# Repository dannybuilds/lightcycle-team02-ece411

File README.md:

# lightcycle-team02-ece411
A repository that'll host the documentation, support info, and source files for Team 02's practicum project.

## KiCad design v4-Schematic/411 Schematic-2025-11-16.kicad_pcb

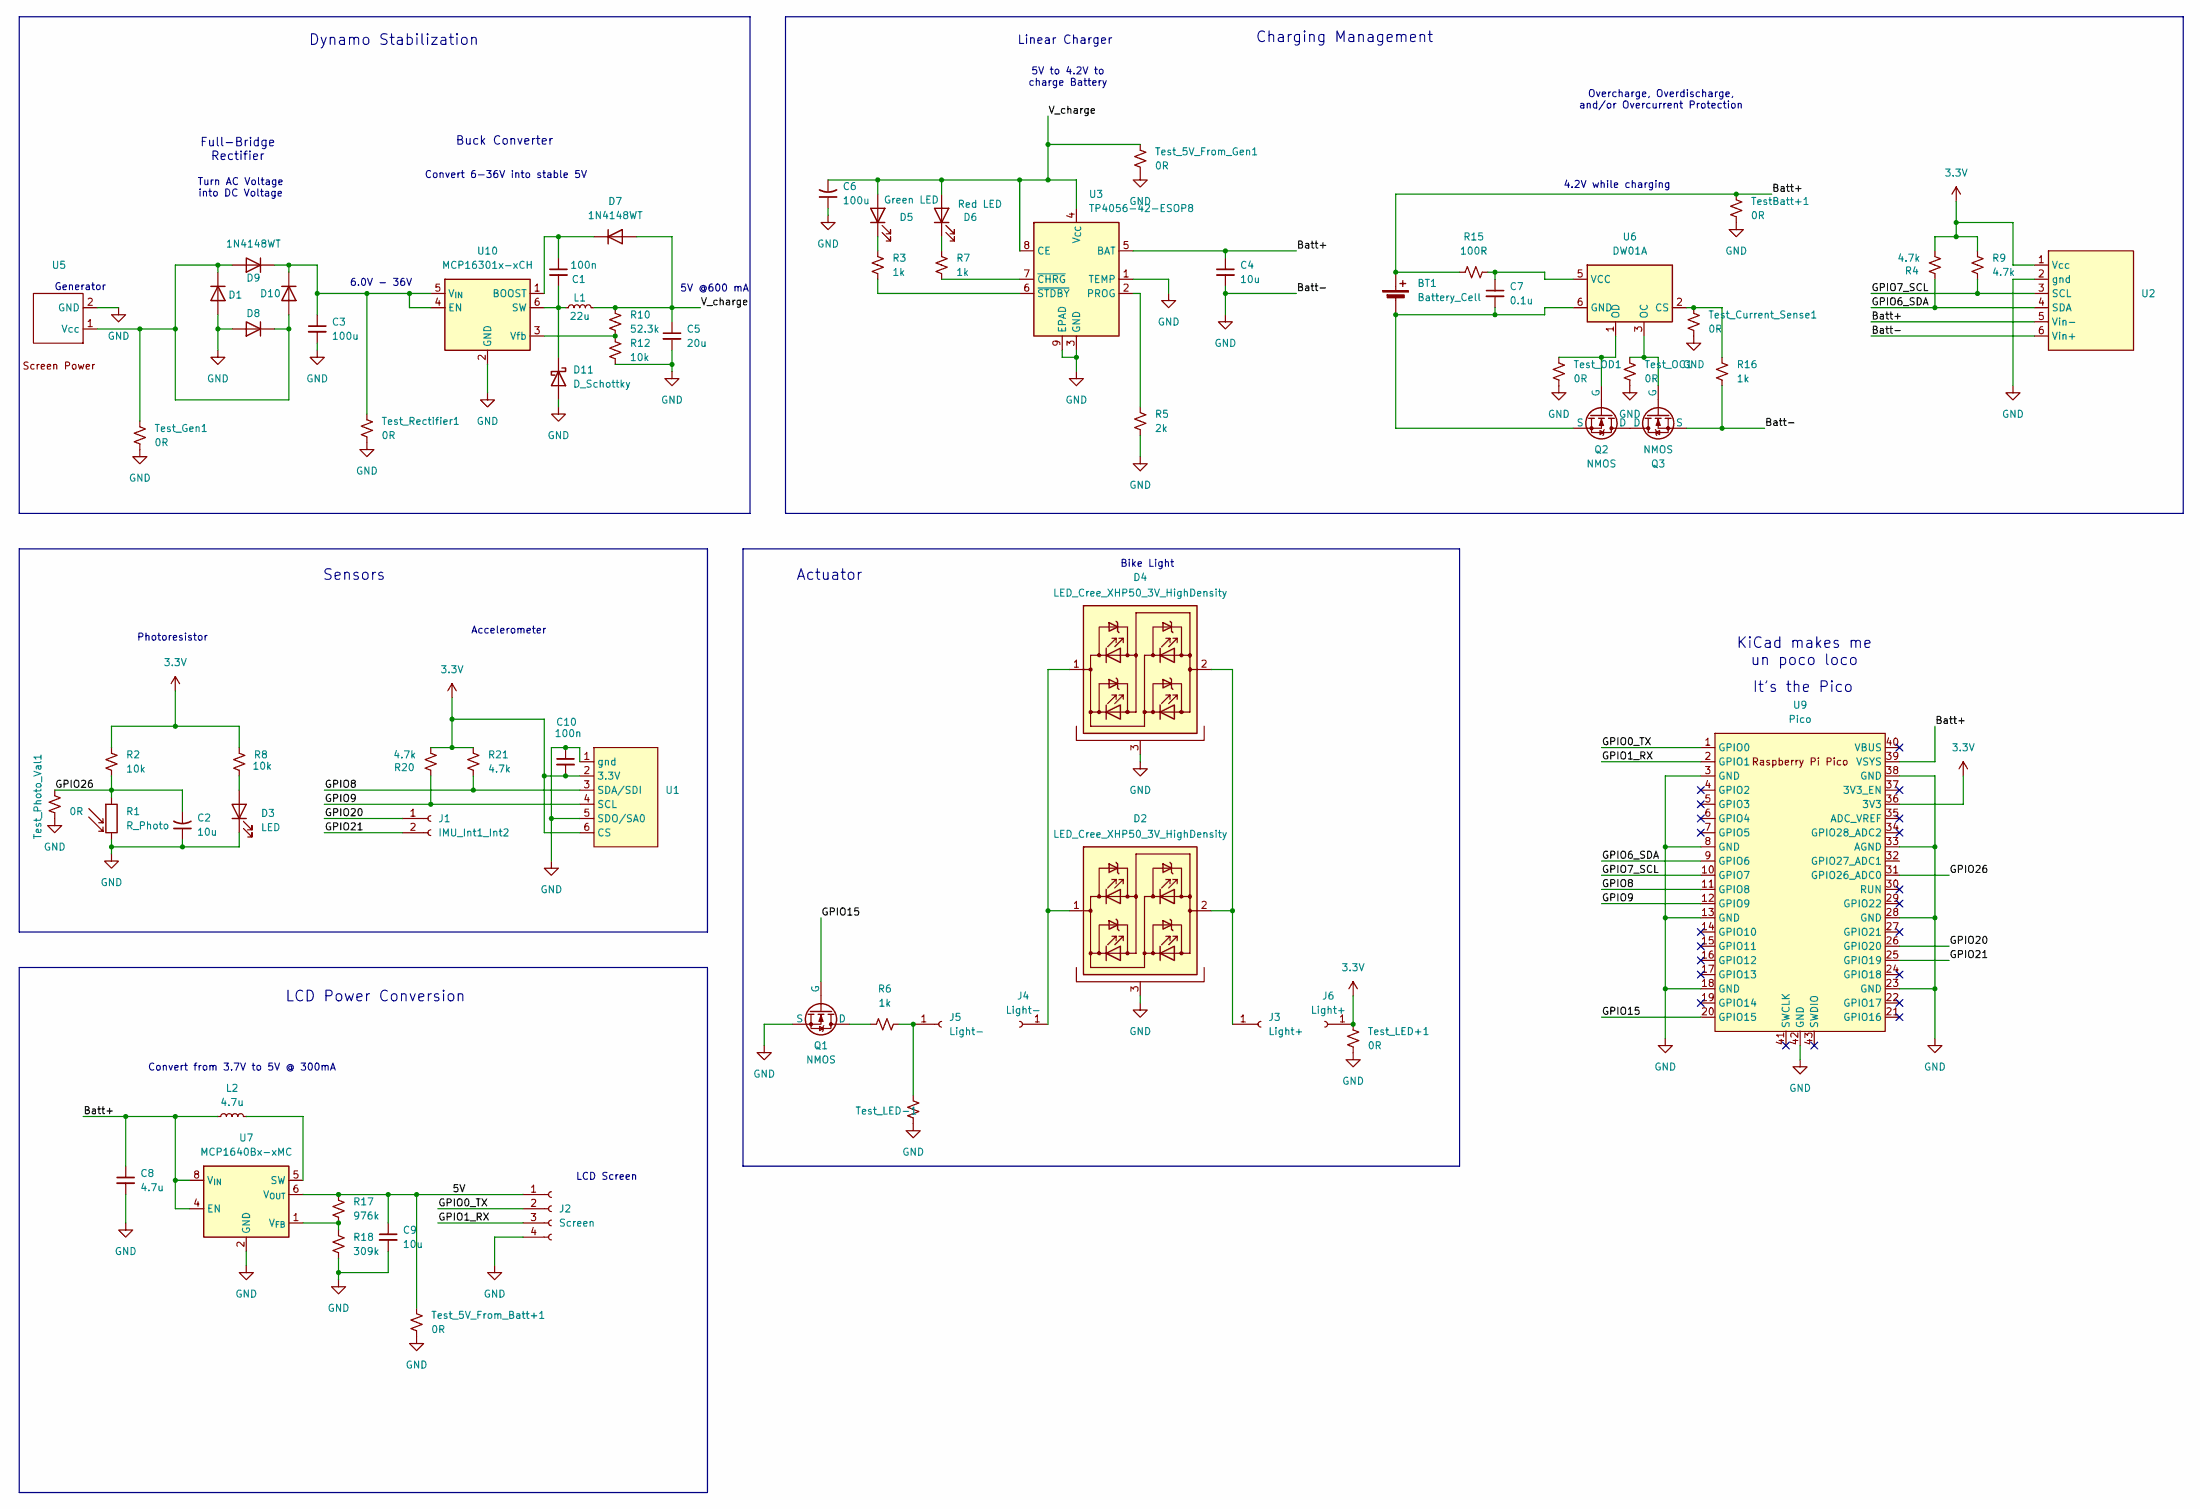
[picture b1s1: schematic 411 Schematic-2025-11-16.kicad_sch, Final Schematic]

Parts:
BT1: Battery_Cell; LED_D3.0mm_Clear
C1, C10: 100n; CP_Radial_D4.0mm_P2.00mm
C2, C4, C9: 10u; CP_Radial_D4.0mm_P2.00mm
C3, C6: 100u; CP_Radial_D4.0mm_P2.00mm
C5: 20u; CP_Radial_D4.0mm_P2.00mm
C7: 0.1u; CP_Radial_D4.0mm_P2.00mm
C8: 4.7u; CP_Radial_D4.0mm_P2.00mm
D1, D7, D8, D9, D10: 1N4148WT; LED_D3.0mm_Clear
D2, D4: LED_Cree_XHP50_3V_HighDensity; LED_Cree-XHP50_3V_HighDensity
D3: LED; LED_D3.0mm_Clear
D5: Green LED; LED_D3.0mm_Clear
D6: Red LED; LED_D3.0mm_Clear
D11: D_Schottky; D_A-405_P7.62mm_Horizontal
J1: IMU_Int1_Int2; PinHeader_2x01_P2.00mm_Vertical
J2: Screen; JST_EH_B6B-EH-A_1x06_P2.50mm_Vertical
J3, J6: Light+; Pin_D0.7mm_L6.5mm_W1.8mm_FlatFork
J4, J5: Light-; Pin_D0.7mm_L6.5mm_W1.8mm_FlatFork
L1: 22u; L_Wuerth_WE-PD-Typ-7345
L2: 4.7u; L_Wuerth_WE-PD-Typ-7345
Q1, Q2, Q3: NMOS; TO-92L_Inline_Wide
R1: R_Photo; R_LDR_4.9x4.2mm_P2.54mm_Vertical
R2, R8, R12: 10k; R_Axial_DIN0207_L6.3mm_D2.5mm_P10.16mm_Horizontal
R3, R6, R7, R16: 1k; R_Axial_DIN0207_L6.3mm_D2.5mm_P10.16mm_Horizontal
R4, R9, R20, R21: 4.7k; R_Axial_DIN0207_L6.3mm_D2.5mm_P10.16mm_Horizontal
R5: 2k; R_Axial_DIN0207_L6.3mm_D2.5mm_P10.16mm_Horizontal
R10: 52.3k; R_Axial_DIN0207_L6.3mm_D2.5mm_P10.16mm_Horizontal
R15: 100R; R_Axial_DIN0207_L6.3mm_D2.5mm_P10.16mm_Horizontal
R17: 976k; R_Axial_DIN0207_L6.3mm_D2.5mm_P10.16mm_Horizontal
R18: 309k; R_Axial_DIN0207_L6.3mm_D2.5mm_P10.16mm_Horizontal
TestBatt+1: 0R; R_0603_1608Metric_Pad0.98x0.95mm_HandSolder
Test_5V_From_Batt+1, Test_5V_From_Gen1: 0R; R_0603_1608Metric_Pad0.98x0.95mm_HandSolder
Test_Current_Sense1: 0R; R_0603_1608Metric_Pad0.98x0.95mm_HandSolder
Test_Gen1: 0R; R_0603_1608Metric_Pad0.98x0.95mm_HandSolder
Test_LED+1: 0R; R_0603_1608Metric_Pad0.98x0.95mm_HandSolder
Test_LED-1: 0R; R_0603_1608Metric_Pad0.98x0.95mm_HandSolder
Test_OC1: 0R; R_0603_1608Metric_Pad0.98x0.95mm_HandSolder
Test_OD1: 0R; R_0603_1608Metric_Pad0.98x0.95mm_HandSolder
Test_Photo_Val1: 0R; R_0603_1608Metric_Pad0.98x0.95mm_HandSolder
Test_Rectifier1: 0R; R_0603_1608Metric_Pad0.98x0.95mm_HandSolder
U1, U2, U5: JST_EH_B6B-EH-A_1x06_P2.50mm_Vertical
U3: TP4056-42-ESOP8; SOIC-8-1EP_3.9x4.9mm_P1.27mm_EP2.41x3.3mm_ThermalVias
U6: DW01A; SOT-23-6
U7: MCP1640Bx-xMC; DFN-8-1EP_3x2mm_P0.5mm_EP1.75x1.45mm
U9: Pico; RPi_Pico_SMD_TH
U10: MCP16301x-xCH; SOT-23-6

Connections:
3.3V: C10.2, J6.1, R2.1, R4.1, R8.1, R9.2, R20.1, R21.2, Test_LED+1.2, U1.2 (3.3V), U1.6 (CS), U2.1 (Vcc), U9.36 (3V3)
/5V: C9.1, J2.1, R17.1, Test_5V_From_Batt+1.2, U7.6 (V_{OUT}), U7.7 (V_{OUT})
/Batt+: BT1.1 (+), C4.1, C8.1, L2.1, R15.1, TestBatt+1.2, U2.5 (Vin-), U3.5 (BAT), U7.4 (EN), U7.8 (V_{IN}), U9.39 (VSYS)
/GPIO0_TX: J2.2, U9.1 (GPIO0)
/GPIO1_RX: J2.3, U9.2 (GPIO1)
/GPIO6_SDA: R4.2, U2.4 (SDA), U9.9 (GPIO6)
/GPIO7_SCL: R9.1, U2.3 (SCL), U9.10 (GPIO7)
/GPIO8: R21.1, U1.3 (SDA/SDI), U9.11 (GPIO8)
/GPIO9: R20.2, U1.4 (SCL), U9.12 (GPIO9)
/GPIO15: Q1.2 (G), U9.20 (GPIO15)
/GPIO20: J1.1, U9.26 (GPIO20)
/GPIO21: J1.2, U9.25 (GPIO19)
/GPIO26: C2.2, R1.1, R2.2, Test_Photo_Val1.2, U9.31 (GPIO26_ADC0)
/GPIO27: U9.32 (GPIO27_ADC1)
/V_charge: C5.1, C6.2, D5.2 (A), D6.2 (A), D7.2 (A), L1.2, R10.1, Test_5V_From_Gen1.2, U3.4 (V_{CC}), U3.8 (CE)
GND: C2.1, C3.2, C4.2, C5.2, C6.1, C8.2, C9.2, C10.1, D1.2 (A), D2.3 (PAD), D3.1 (K), D4.3 (PAD), D8.2 (A), D11.2 (A), J2.4, Q1.3 (S), Q3.3 (S), R1.2, R5.2, R12.2, R16.1, R18.2, TestBatt+1.1, Test_5V_From_Batt+1.1, Test_5V_From_Gen1.1, Test_Current_Sense1.1, Test_Gen1.1, Test_LED+1.1, Test_LED-1.1, Test_OC1.1, Test_OD1.1, Test_Photo_Val1.1, Test_Rectifier1.1, U1.1 (gnd), U1.5 (SDO/SA0), U2.2 (gnd), U2.6 (Vin+), U3.1 (TEMP), U3.3 (GND), U3.9 (EPAD), U5.2 (GND), U7.2 (GND), U7.3 (GND), U7.9 (GND), U9.3 (GND), U9.8 (GND), U9.13 (GND), U9.18 (GND), U9.23 (GND), U9.28 (GND), U9.33 (AGND), U9.38 (GND), U9.42 (GND), U10.2 (GND)
unnamed: BT1.2 (-), C7.2, Q2.3 (S), U6.6 (GND)
unnamed: D1.1 (K), D8.1 (K), D9.2 (A), D10.2 (A), Test_Gen1.2, U5.1 (Vcc)
unnamed: D2.2 (A), D4.2 (A), J3.1
unnamed: D2.1 (K), D4.1 (K), J4.1
unnamed: D3.2 (A), R8.2
unnamed: D5.1 (K), R3.1
unnamed: D6.1 (K), R7.1
unnamed: C1.1, D7.1 (K), U10.1 (BOOST)
unnamed: C3.1, D9.1 (K), D10.1 (K), Test_Rectifier1.2, U10.4 (EN), U10.5 (V_{IN})
unnamed: C1.2, D11.1 (K), L1.1, U10.6 (SW)
unnamed: J5.1, R6.2, Test_LED-1.2
unnamed: Q1.1 (D), R6.1
unnamed: Q2.1 (D), Q3.1 (D)
unnamed: Q2.2 (G), Test_OD1.2, U6.1 (OD)
unnamed: Q3.2 (G), Test_OC1.2, U6.3 (OC)
unnamed: R5.1, U3.2 (PROG)
unnamed: R7.2, U3.7 (~CHRG)
unnamed: R3.2, U3.6 (~STDBY)
unnamed: R16.2, Test_Current_Sense1.2, U6.2 (CS)
unnamed: C7.1, R15.2, U6.5 (VCC)
unnamed: L2.2, U7.5 (SW)
unnamed: R17.2, R18.1, U7.1 (V_{FB})
unnamed: R10.2, R12.1, U10.3 (Vfb)

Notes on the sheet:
Dynamo Stabilization
Buck Converter
Convert from 3.7V to 5V @ 300mA
Overcharge, Overdischarge, and/or Overcurrent Protection
Actuator
KiCad makes me un poco loco
Full-Bridge Rectifier
It's the Pico
6.0V - 36V
Accelerometer
LCD Power Conversion
Convert 6-36V into stable 5V
Linear Charger
LCD Screen
Sensors
5V @600 mA
Turn AC Voltage into DC Voltage
Photoresistor
Generator
5V to 4.2V to charge Battery
Charging Management
Bike Light
4.2V while charging

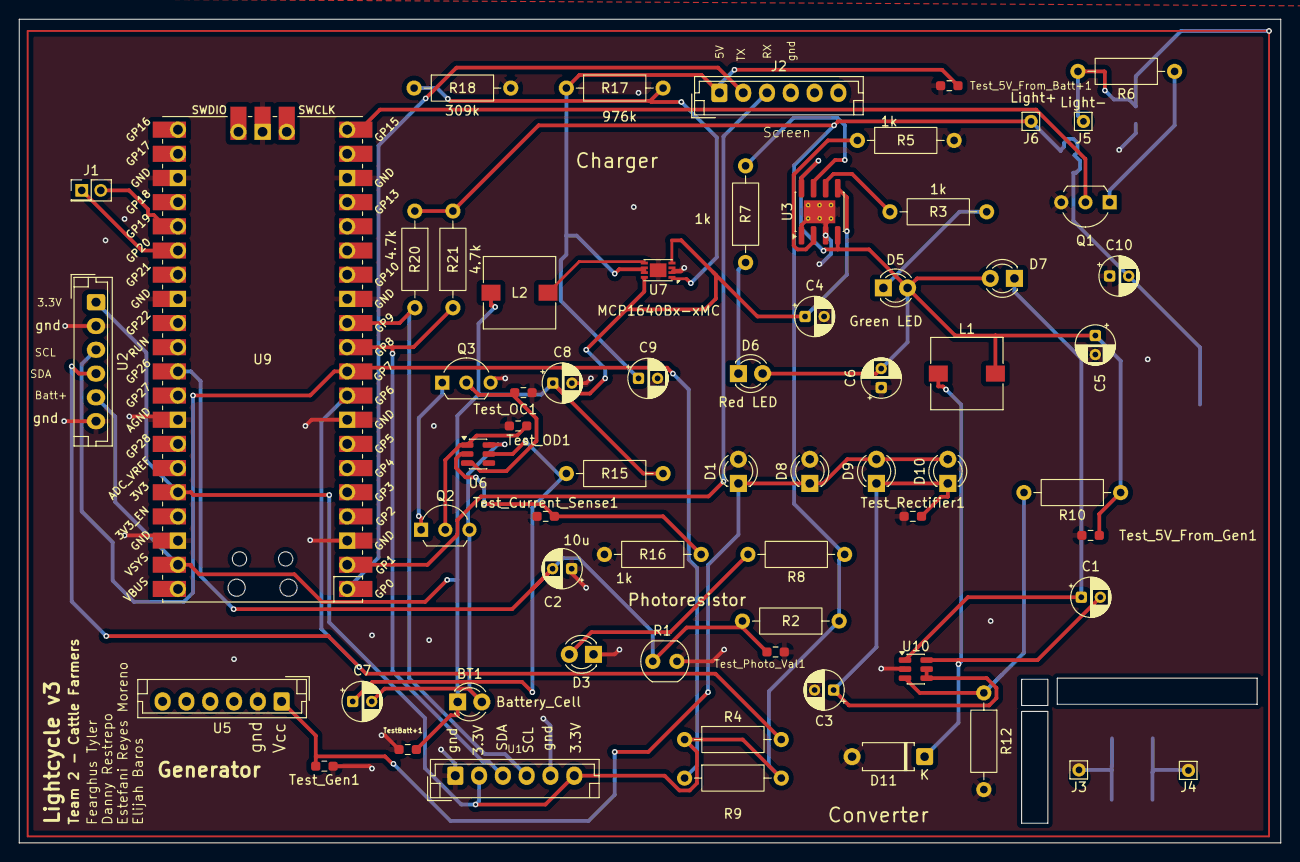
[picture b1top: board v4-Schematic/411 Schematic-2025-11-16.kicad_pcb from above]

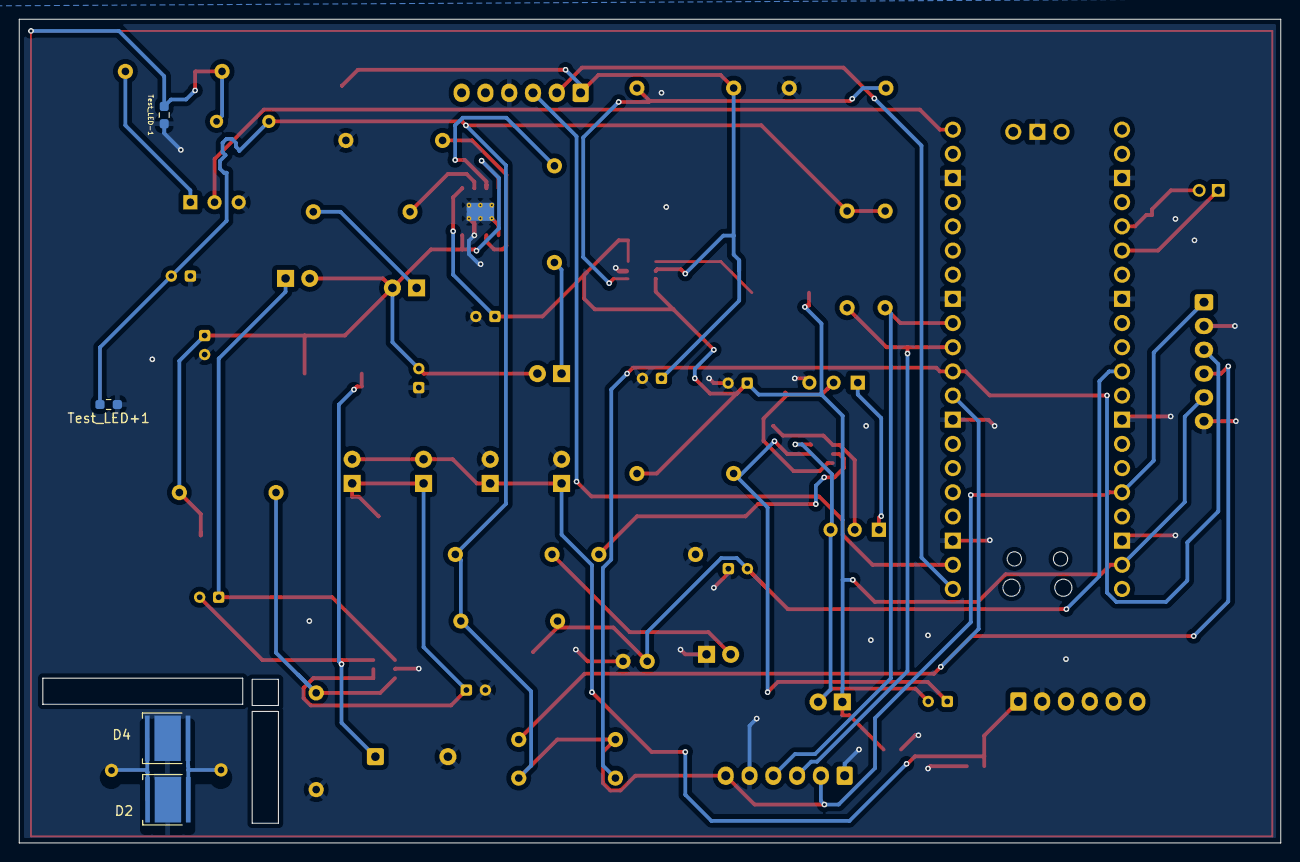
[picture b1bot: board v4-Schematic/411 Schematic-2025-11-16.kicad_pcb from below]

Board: 2 copper layers, 132.5 x 86.5 mm, 69 parts (4 on the bottom side), 38 nets.

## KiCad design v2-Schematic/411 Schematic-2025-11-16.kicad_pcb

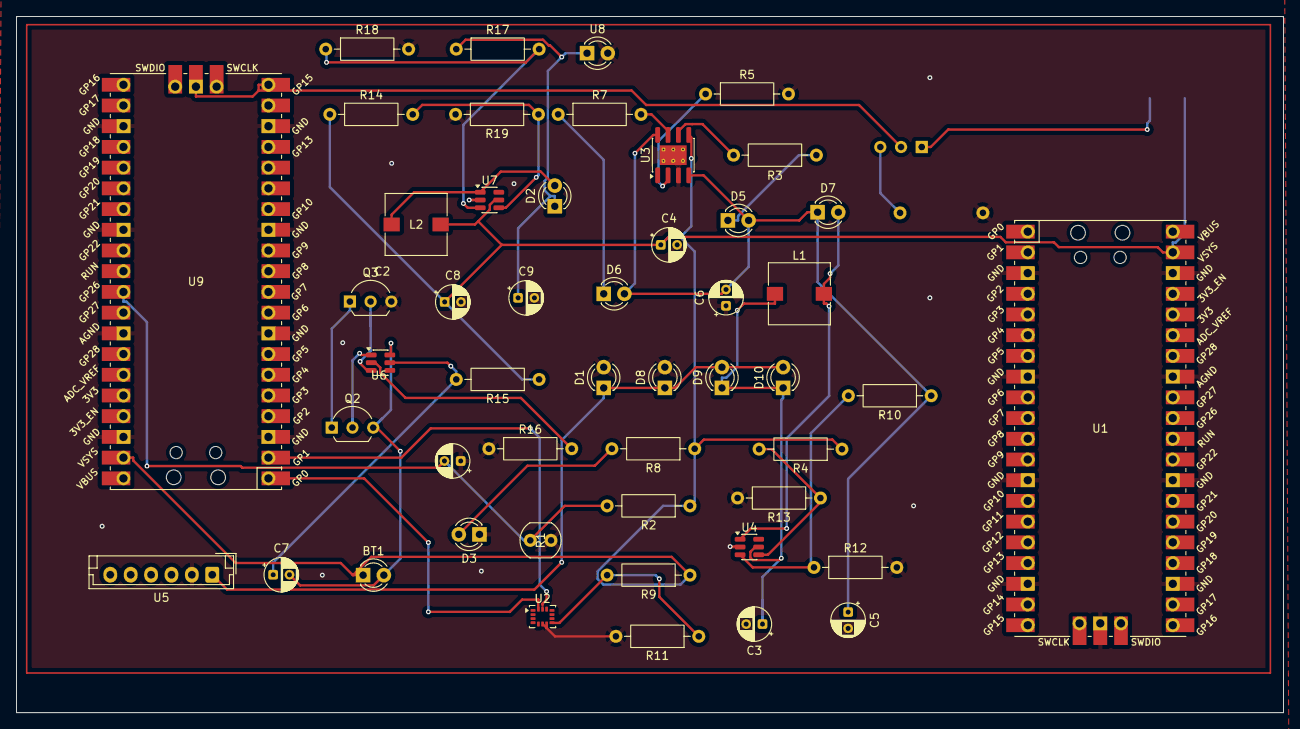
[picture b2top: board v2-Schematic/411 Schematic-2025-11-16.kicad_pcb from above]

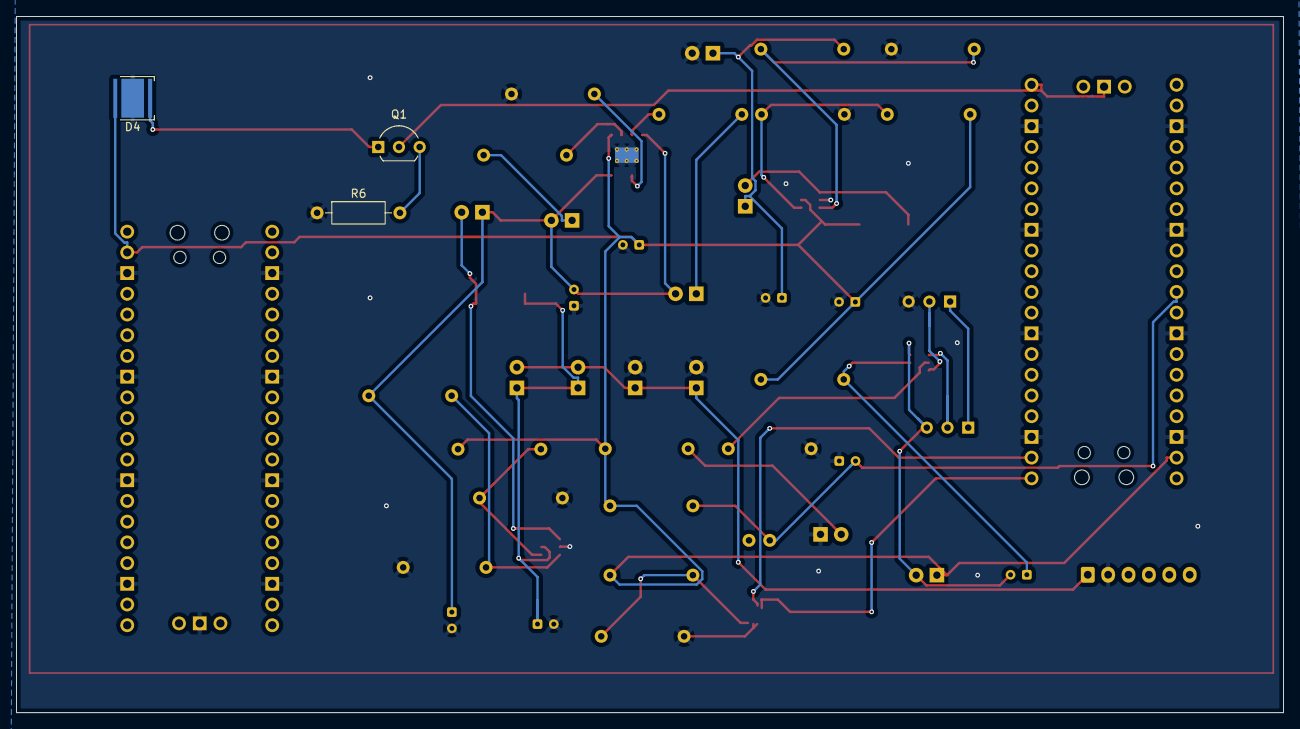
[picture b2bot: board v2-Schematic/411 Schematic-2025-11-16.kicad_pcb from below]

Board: 2 copper layers, 155.4 x 85.4 mm, 52 parts (3 on the bottom side), 31 nets.

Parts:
BT1: Battery_Cell; LED_D3.0mm_Clear
C2, C4: 10u; CP_Radial_D4.0mm_P2.00mm
C3, C5, C6, C8, C9: 100u; CP_Radial_D4.0mm_P2.00mm
C7: 0.1u; CP_Radial_D4.0mm_P2.00mm
D1, D2, D7, D8, D9, D10: 1N4148WT; LED_D3.0mm_Clear
D3, D5, D6: LED; LED_D3.0mm_Clear
D4: LED_Cree_XHP50_3V_HighDensity; LED_Cree-XHP50_3V_HighDensity
L1, L2: 1n; L_Wuerth_WE-PD-Typ-7345
Q1, Q2, Q3: NMOS; TO-92L_Inline_Wide
R1: R_Photo; R_LDR_4.9x4.2mm_P2.54mm_Vertical
R2, R8, R10, R12, R18: 10k; R_Axial_DIN0207_L6.3mm_D2.5mm_P10.16mm_Horizontal
R3, R4, R5, R6, R7, R9, R11, R13, R14, R16, R19: 1k; R_Axial_DIN0207_L6.3mm_D2.5mm_P10.16mm_Horizontal
R15: 100R; R_Axial_DIN0207_L6.3mm_D2.5mm_P10.16mm_Horizontal
R17: 3.5k; R_Axial_DIN0207_L6.3mm_D2.5mm_P10.16mm_Horizontal
U1, U9: Pico; RPi_Pico_SMD_TH
U2: LSM6DS3; LGA-14_3x2.5mm_P0.5mm_LayoutBorder3x4y
U3: TP4056-42-ESOP8; SOIC-8-1EP_3.9x4.9mm_P1.27mm_EP2.41x3.3mm_ThermalVias
U4, U7: MT3608; SOT-23-6
U5: JST_EH_B6B-EH-A_1x06_P2.50mm_Vertical
U6: DW01A; SOT-23-6
U8: LED_D3.0mm_Clear

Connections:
3.7V: BT1.1 (+), C4.1, C8.1, D4.2 (A), L2.1, R2.1, R4.1, R8.1, R9.1, R14.1, R15.1, U1.39 (VSYS), U3.5 (BAT), U7.5 (IN), U9.39 (VSYS)
/5V: C9.1, D2.1 (K), R17.1, U8.1 (Vcc)
/GPIO0: U2.14 (SDA), U9.1 (GPIO0)
/GPIO1: U2.13 (SCL), U9.2 (GPIO1)
/GPIO15: Q1.2 (G), U9.20 (GPIO15), U9.42 (GND)
/GPIO26: C2.2, R1.1, R2.2, U9.31 (GPIO26_ADC0)
/V_charge: C5.1, C6.2, D5.2 (A), D6.2 (A), D7.1 (K), R10.1, U3.4 (V_{CC}), U3.8 (CE)
GND: C2.1, C3.2, C4.2, C5.2, C6.1, C8.2, C9.2, D1.2 (A), D3.1 (K), D4.3 (PAD), D8.2 (A), Q3.3 (S), R1.2, R5.2, R6.1, R11.2, R12.2, R13.2, R16.1, R18.2, R19.2, U1.3 (GND), U1.8 (GND), U1.13 (GND), U1.18 (GND), U1.23 (GND), U1.28 (GND), U1.33 (AGND), U1.38 (GND), U1.42 (GND), U2.6 (GND), U2.7 (GND), U3.3 (GND), U3.9 (EPAD), U4.2 (GND), U5.2 (GND), U7.2 (GND), U8.2 (GND), U9.3 (GND), U9.8 (GND), U9.13 (GND), U9.18 (GND), U9.23 (GND), U9.28 (GND), U9.33 (AGND), U9.38 (GND)
unnamed: BT1.2 (-), C7.2, Q2.3 (S), U6.6 (GND)
unnamed: D1.1 (K), D8.1 (K), D9.2 (A), D10.2 (A), U5.1 (Vcc)
unnamed: D2.2 (A), L2.2, U7.1 (SW)
unnamed: D3.2 (A), R8.2
unnamed: D4.1 (K), Q1.1 (D)
unnamed: D5.1 (K), R3.1
unnamed: D6.1 (K), R7.1
unnamed: D7.2 (A), L1.2, U4.1 (SW)
unnamed: C3.1, D9.1 (K), D10.1 (K), L1.1, U4.5 (IN)
unnamed: Q1.3 (S), R6.2
unnamed: Q2.1 (D), Q3.1 (D)
unnamed: Q2.2 (G), U6.1 (OD)
unnamed: Q3.2 (G), U6.3 (OC)
unnamed: R9.2, R11.1, U2.8 (VDD)
unnamed: R5.1, U3.2 (PROG)
unnamed: R7.2, U3.7 (~CHRG)
unnamed: R3.2, U3.6 (~STDBY)
unnamed: R4.2, R13.1, U4.4 (EN)
unnamed: R10.2, R12.1, U4.3 (FB)
unnamed: R16.2, U6.2 (CS)
unnamed: C7.1, R15.2, U6.5 (VCC)
unnamed: R14.2, R19.1, U7.4 (EN)
unnamed: R17.2, R18.1, U7.3 (FB)

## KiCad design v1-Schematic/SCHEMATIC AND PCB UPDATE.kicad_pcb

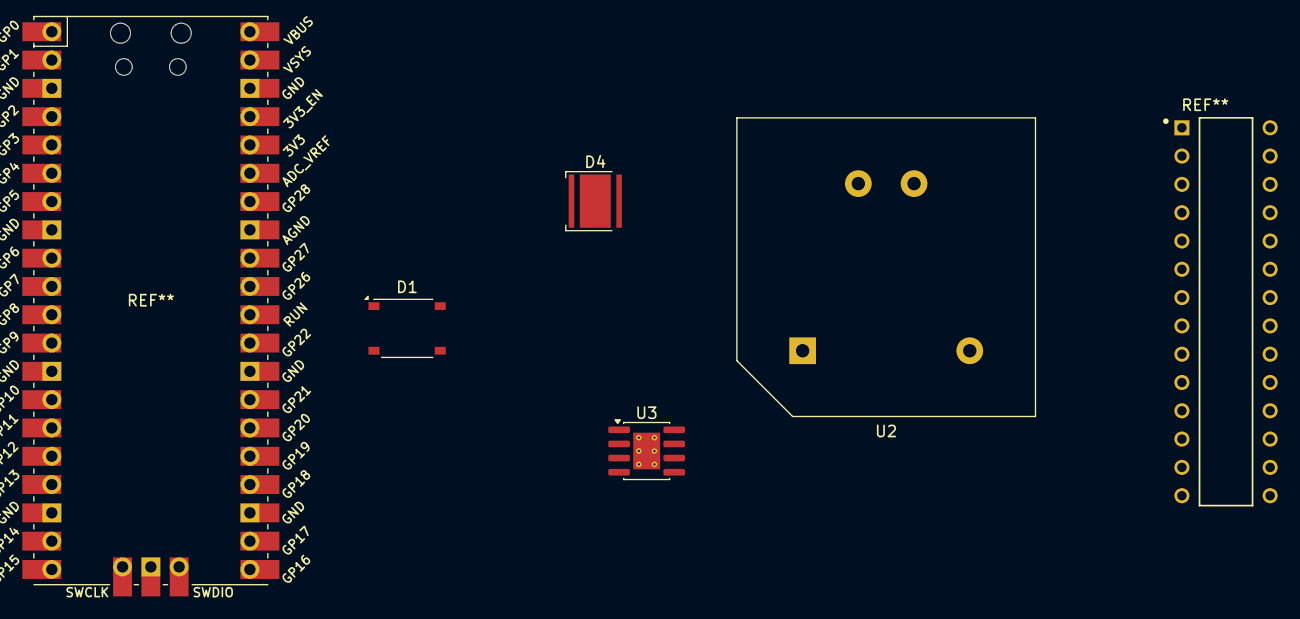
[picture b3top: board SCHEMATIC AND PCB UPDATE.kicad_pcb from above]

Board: 2 copper layers, 4 parts (0 on the bottom side), 2 nets, no tracks yet.

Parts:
D1: ABS2; Diode_Bridge_Diotec_ABS
D4: LED_Cree_XHP50_3V_HighDensity; LED_Cree-XHP50_3V_HighDensity
U2: TL5001; Converter_ACDC_ZETTLER_ZPI03Sxx00WC_THT
U3: TP4056-42-ESOP8; SOIC-8-1EP_3.9x4.9mm_P1.27mm_EP2.41x3.3mm_ThermalVias

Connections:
GND: D4.1 (K), D4.3 (PAD), U3.3 (GND)
VCC: D4.2 (A), U3.4 (V_{CC})

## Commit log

2025-10-16 Rename repository title in README
2025-10-30 Preliminary schematic design
2025-10-30 Preliminary schematic design, second version
2025-11-08 Adding Week 06 submission files
2025-11-08 Restructuring project files & adding Updated Schematic
2025-11-20 Updated schematic to reflect post-design-review feedback
2025-11-20 Refreshed directory and schematic version control scheme
2025-11-20 Refreshed directory and schematic version control scheme (again)
2025-11-20 Added v2 and v3 of our project schematic & PCB
2025-11-20 Added final v4 of our project schematic & PCB
2025-11-20 Final CAD Submission for Team 02
2025-11-20 Added the final PDF version of our CAD submission.
